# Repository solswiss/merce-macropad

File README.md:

# merce-macropad
A minimal 9-key macropad with an OLED display and RGB backlighting. The result of my first venture into keebs!....... The product of sleepless nights...

## BOM
|part                      |#|
|--------------------------|-|
|Seeed XIAO RP2040         |1|
|Through-hole 1N4148 Diodes|9|
|MX-Style switches         |9|
|0.91 inch OLED displays   |1|
|Blank DSA keycaps         |9|
|SK6812 MINI-E LEDs        |9|
|500ohm resistors*         |1|
|M3x16mm screws            |4|
|M3x5mx4mm heatset inserts |4|

*can supply personally

## Gallery
![schematic made with kicad][schematic]
![pcb made with kicad][pcb]
![render with bare pcb made with fusion360][render-bare]
![render with bare pcb made with fusion360][render-bare-1]
![render with mockup pcb made with fusion360][render-mockup]

[schematic]:https://github.com/solswiss/merce-macropad/blob/main/assets/schematic.png
[pcb]:https://github.com/solswiss/merce-macropad/blob/main/assets/pcb.png
[render-bare]:https://github.com/solswiss/merce-macropad/blob/main/assets/bare-render.png
[render-bare-1]:https://github.com/solswiss/merce-macropad/blob/main/assets/bare-render-top.png
[render-mockup]:https://github.com/solswiss/merce-macropad/blob/main/assets/render-mockup.png

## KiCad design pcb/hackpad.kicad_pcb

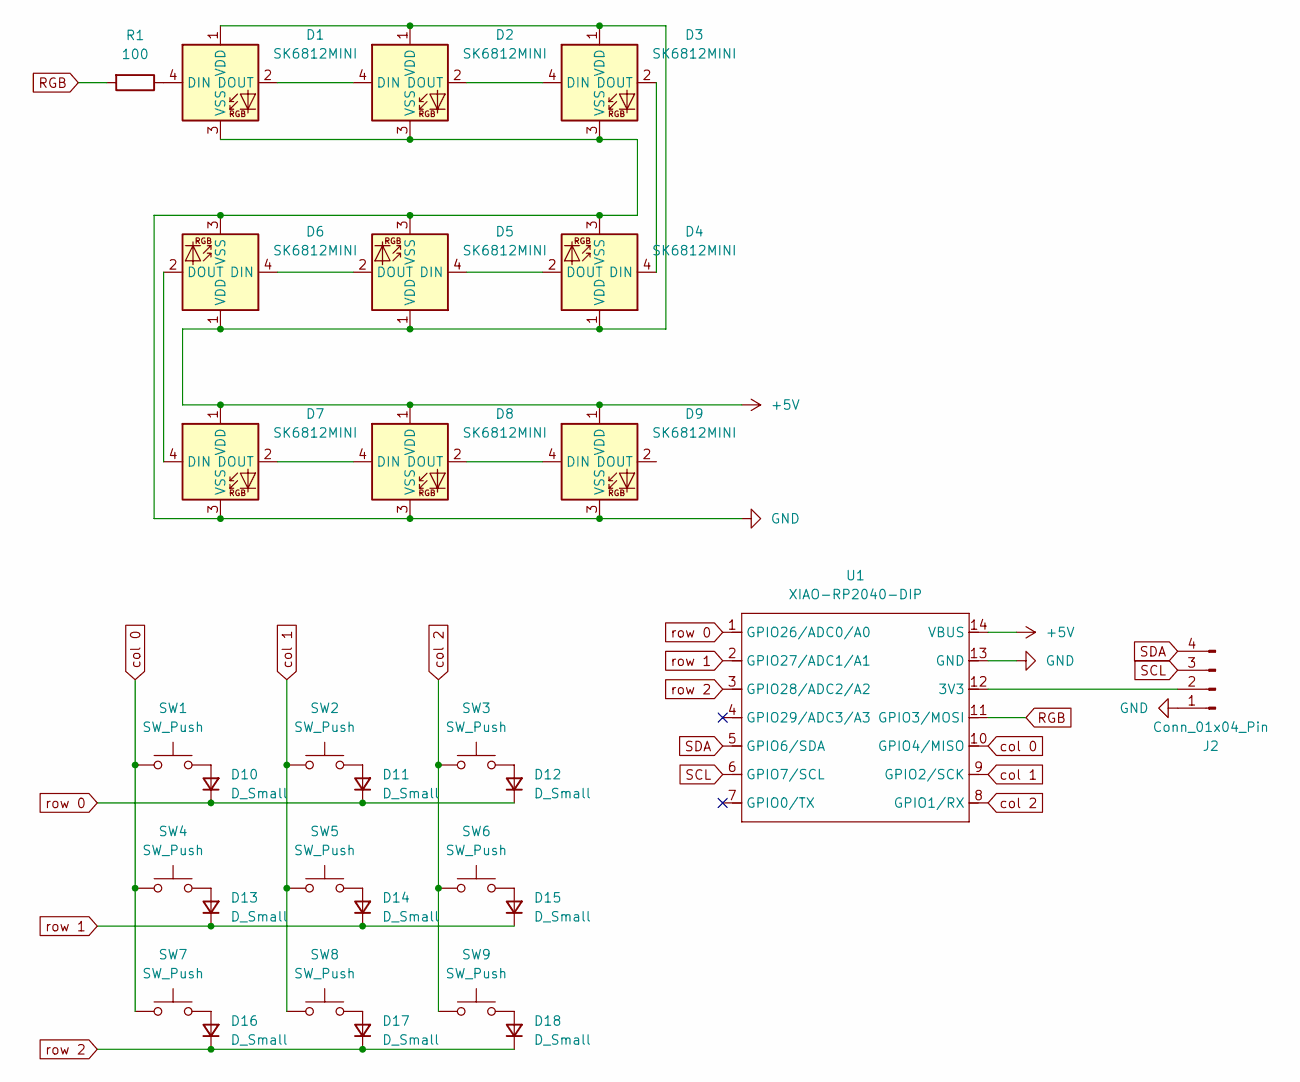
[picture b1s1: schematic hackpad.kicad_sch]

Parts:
D1, D2, D3, D4, D5, D6, D7, D8, D9: SK6812MINI; yta-SK6812MINI-E
D10, D11, D12, D13, D14, D15, D16, D17, D18: D_Small; Diode_DO-35
J2: Conn_01x04_Pin; SSD1306-0.91-OLED-4pin-128x32
R1: 100; R_Axial_DIN0204_L3.6mm_D1.6mm_P5.08mm_Vertical
SW1, SW2, SW3, SW4, SW5, SW6, SW7, SW8, SW9: SW_Push; SW_Cherry_MX_1.00u_PCB
U1: XIAO-RP2040-DIP

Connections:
+5V: D1.1 (VDD), D2.1 (VDD), D3.1 (VDD), D4.1 (VDD), D5.1 (VDD), D6.1 (VDD), D7.1 (VDD), D8.1 (VDD), D9.1 (VDD), U1.14 (VBUS)
GND: D1.3 (VSS), D2.3 (VSS), D3.3 (VSS), D4.3 (VSS), D5.3 (VSS), D6.3 (VSS), D7.3 (VSS), D8.3 (VSS), D9.3 (VSS), J2.1, U1.13 (GND)
unnamed: D1.4 (DIN), R1.1
unnamed: D1.2 (DOUT), D2.4 (DIN)
unnamed: D2.2 (DOUT), D3.4 (DIN)
unnamed: D3.2 (DOUT), D4.4 (DIN)
unnamed: D4.2 (DOUT), D5.4 (DIN)
unnamed: D5.2 (DOUT), D6.4 (DIN)
unnamed: D6.2 (DOUT), D7.4 (DIN)
unnamed: D7.2 (DOUT), D8.4 (DIN)
unnamed: D8.2 (DOUT), D9.4 (DIN)
unnamed: D10.2 (A), SW1.2
unnamed: D11.2 (A), SW2.2
unnamed: D12.2 (A), SW3.2
unnamed: D13.2 (A), SW4.2
unnamed: D14.2 (A), SW5.2
unnamed: D15.2 (A), SW6.2
unnamed: D16.2 (A), SW7.2
unnamed: D17.2 (A), SW8.2
unnamed: D18.2 (A), SW9.2
unnamed: J2.2, U1.12 (3V3)
RGB: R1.2, U1.11 (GPIO3/MOSI)
SCL: J2.3, U1.6 (GPIO7/SCL)
SDA: J2.4, U1.5 (GPIO6/SDA)
col 0: SW1.1, SW4.1, SW7.1, U1.10 (GPIO4/MISO)
col 1: SW2.1, SW5.1, SW8.1, U1.9 (GPIO2/SCK)
col 2: SW3.1, SW6.1, SW9.1, U1.8 (GPIO1/RX)
row 0: D10.1 (K), D11.1 (K), D12.1 (K), U1.1 (GPIO26/ADC0/A0)
row 1: D13.1 (K), D14.1 (K), D15.1 (K), U1.2 (GPIO27/ADC1/A1)
row 2: D16.1 (K), D17.1 (K), D18.1 (K), U1.3 (GPIO28/ADC2/A2)

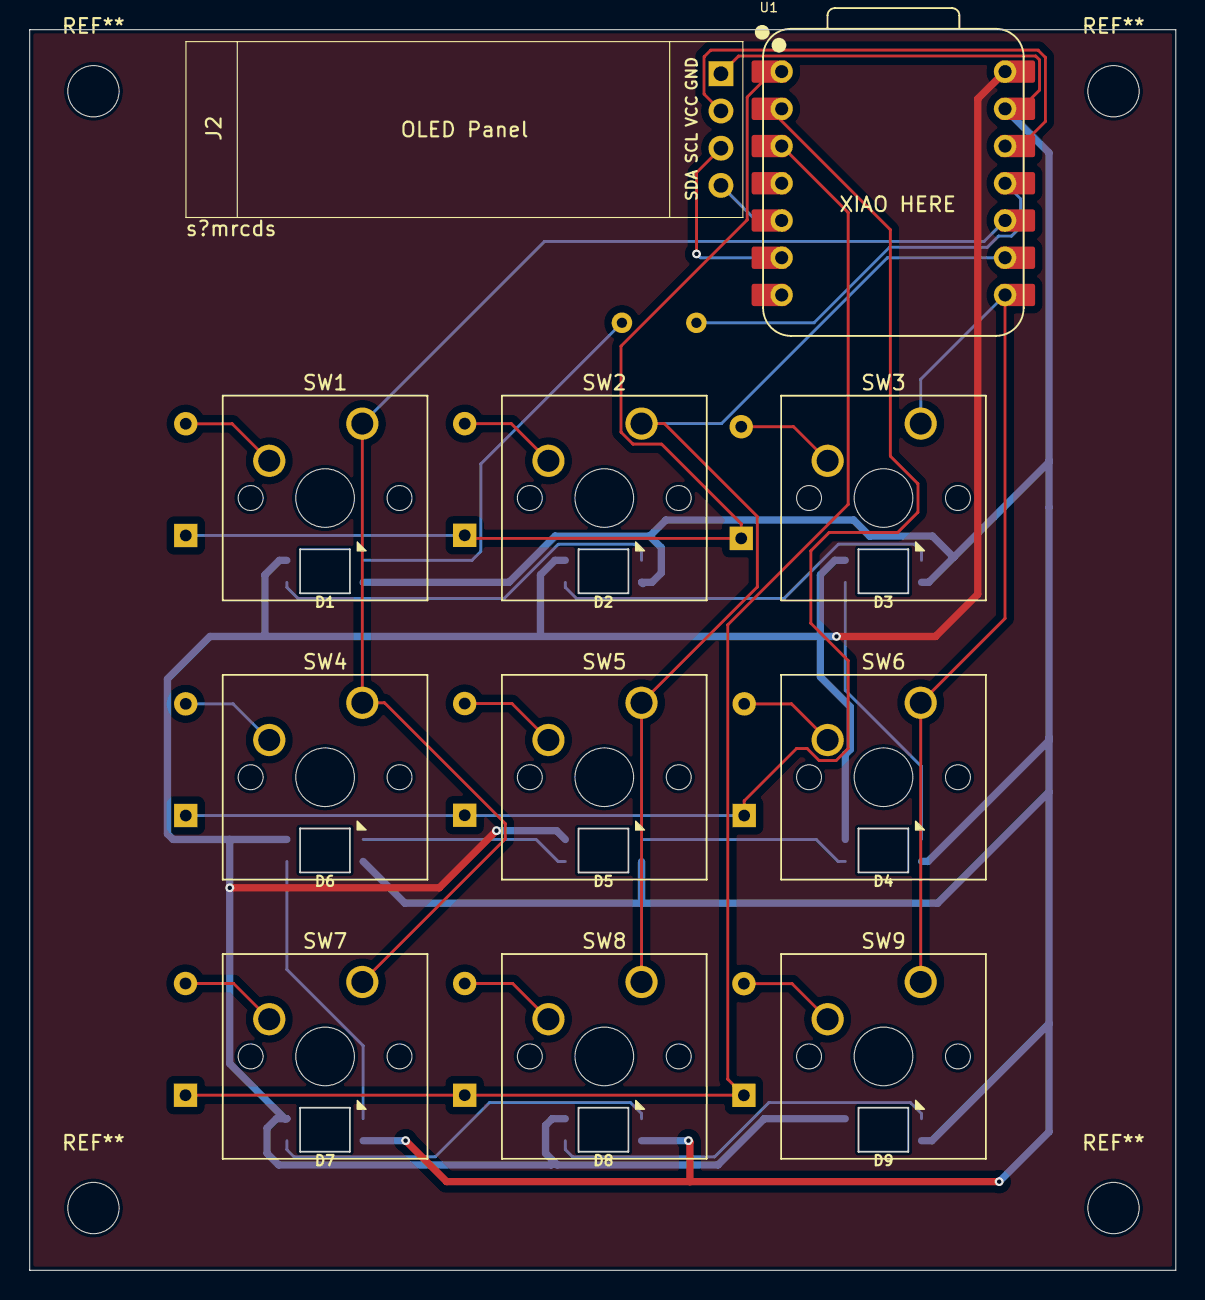
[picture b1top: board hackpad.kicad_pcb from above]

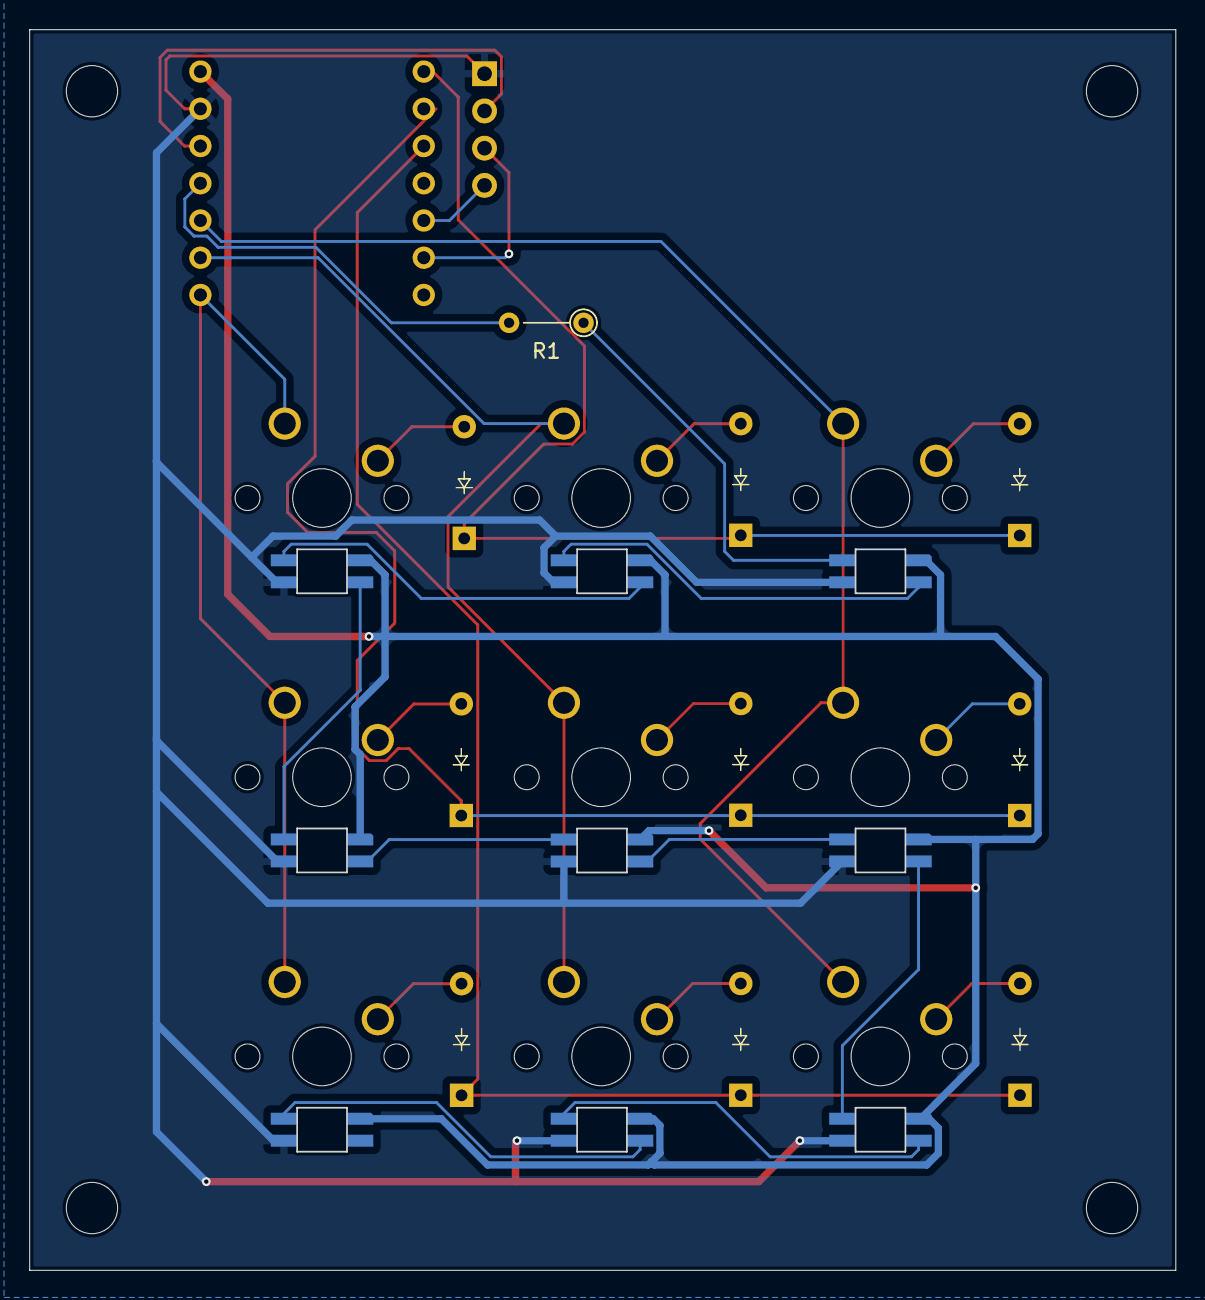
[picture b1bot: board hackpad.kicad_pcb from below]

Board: 2 copper layers, 78.2 x 84.7 mm, 30 parts (10 on the bottom side), 30 nets.

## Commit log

2025-07-01 changed top - update overall cad
2025-07-01 Changed top
2025-07-07 Delete cad/case-cad.step
    update
